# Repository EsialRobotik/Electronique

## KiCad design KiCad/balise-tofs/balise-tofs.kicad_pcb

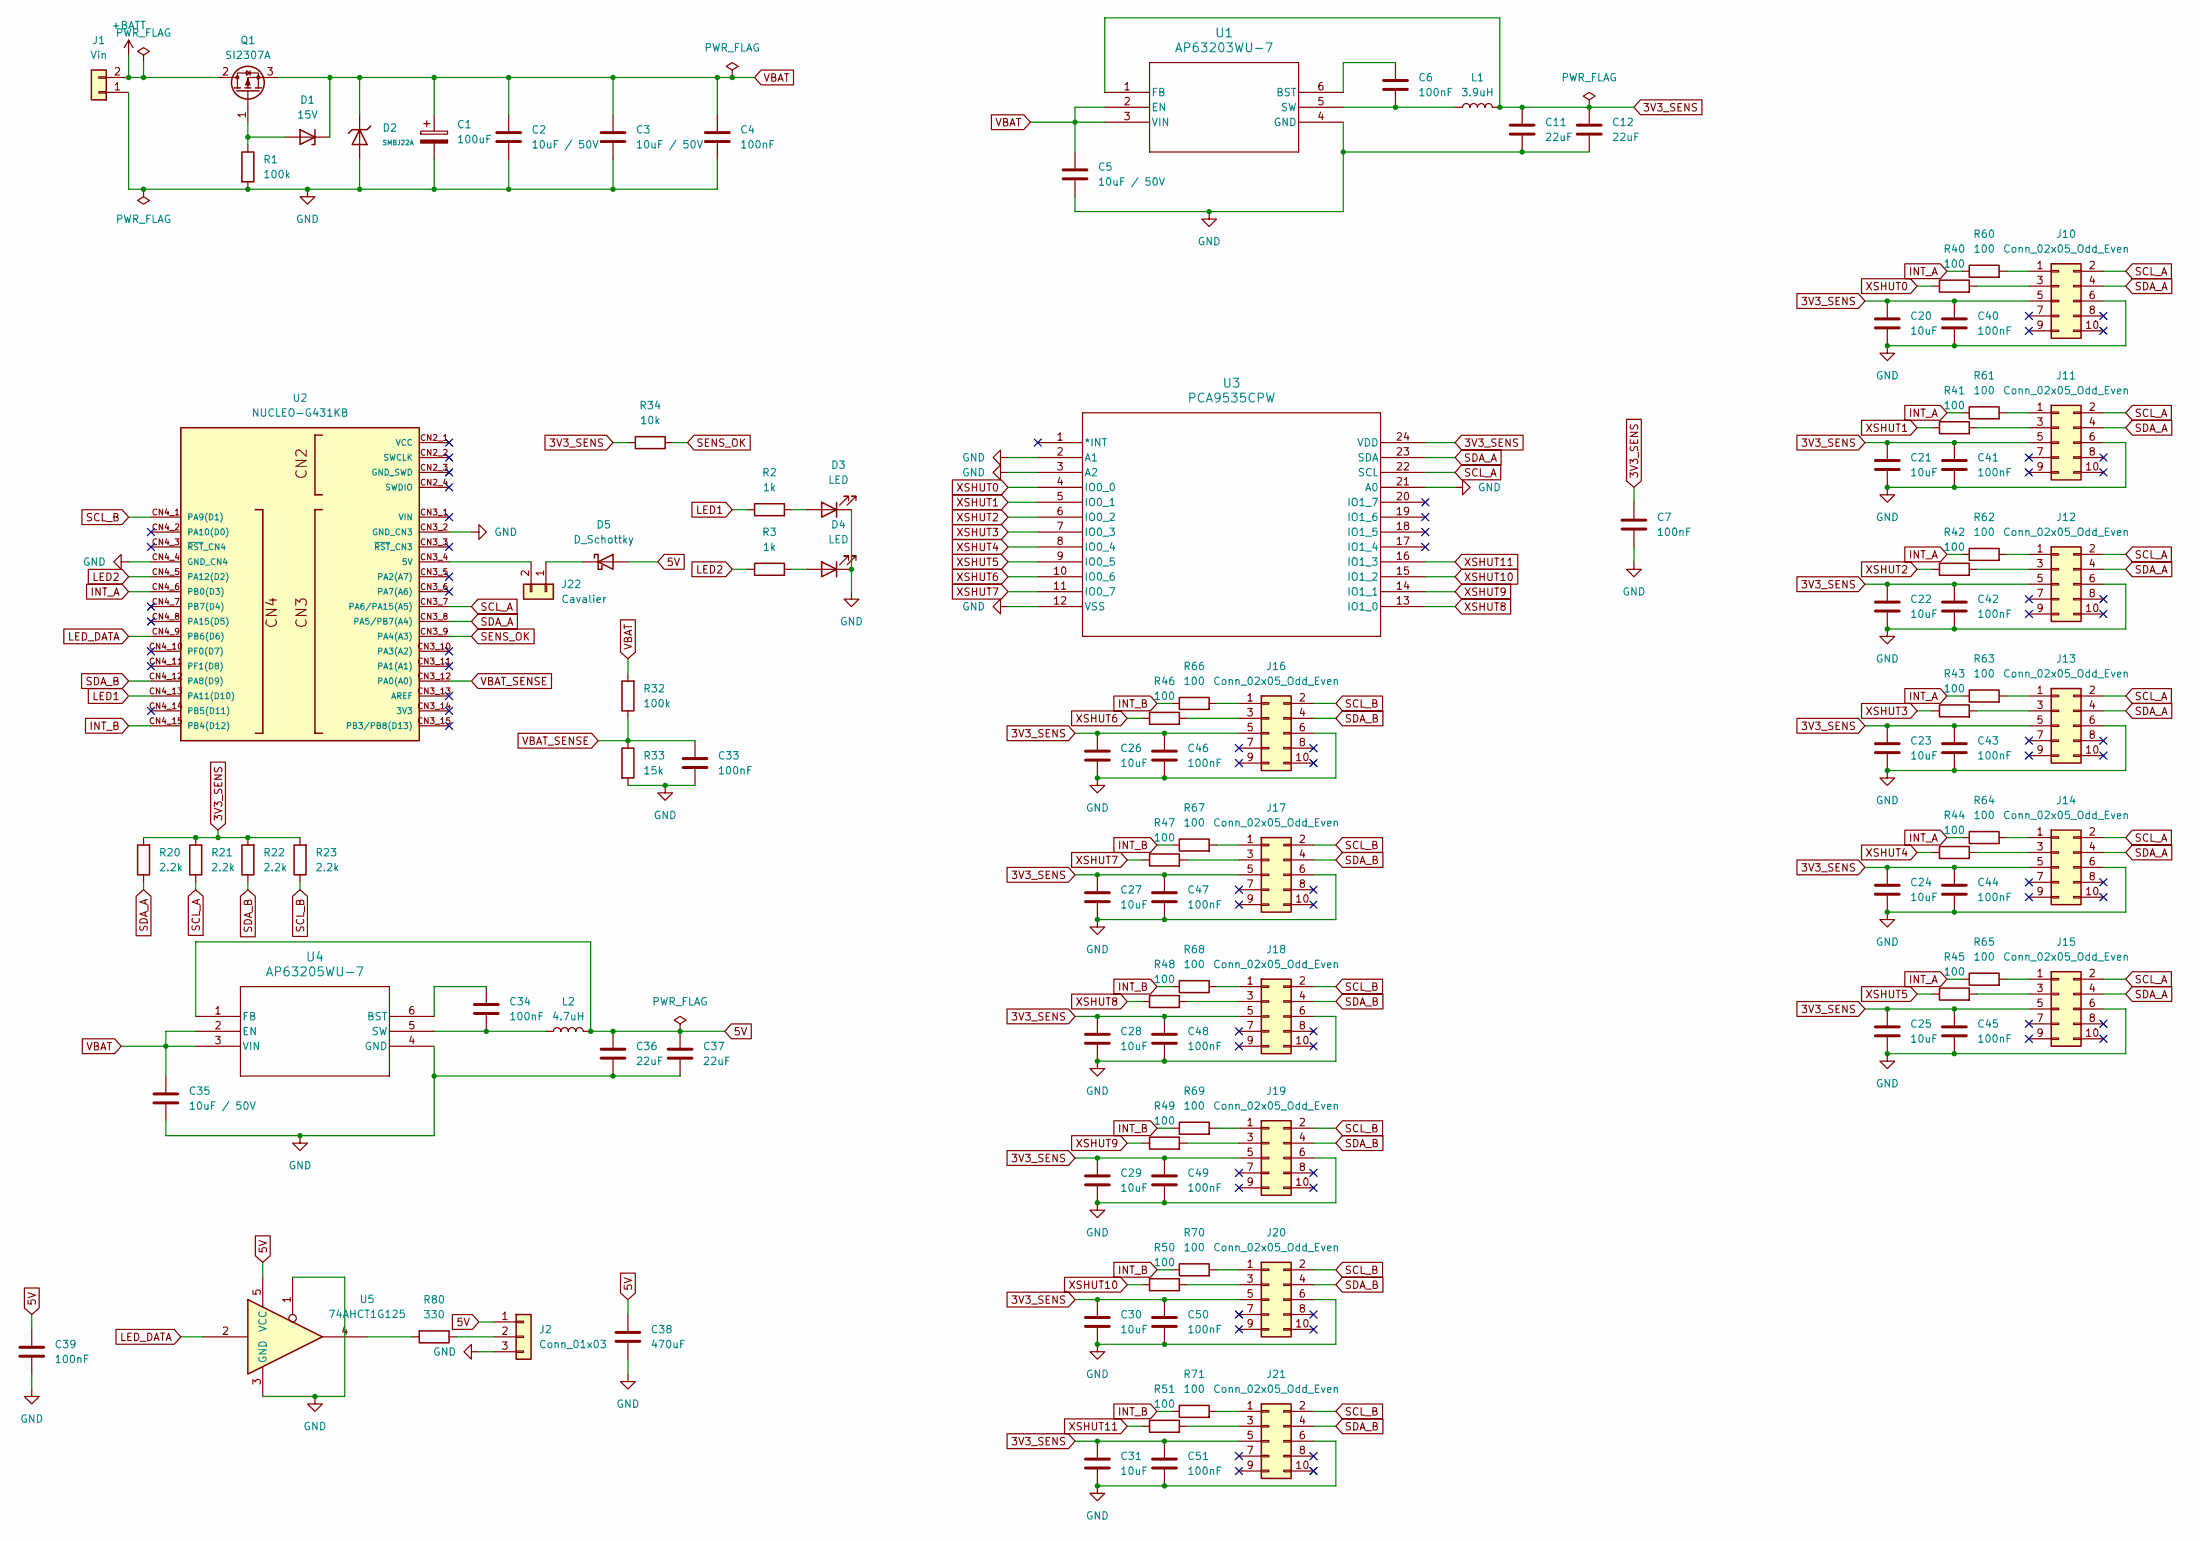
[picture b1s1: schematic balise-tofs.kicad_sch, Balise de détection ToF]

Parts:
C1: 100uF; CP_Elec_8x10.5; LCSC C165580
C2, C3, C5, C35: 10uF / 50V; C_1210_3225Metric; LCSC C138687
C4, C6, C7, C33, C34, C39, C40, C41, C42, C43, C44, C45, C46, C47, C48, C49, C50, C51: 100nF; C_0603_1608Metric; LCSC C14663
C11, C12, C36, C37: 22uF; C_1210_3225Metric; LCSC C52306
C20, C21, C22, C23, C24, C25, C26, C27, C28, C29, C30, C31: 10uF; C_0805_2012Metric; LCSC C15850
C38: 470uF; CP_Elec_8x10.5; LCSC C165531
D1: 15V; D_SOD-123; LCSC C173427
D2: SMBJ22A; D_SMB; Part SMBJ24A; LCSC C151920
D3: LED; LED_0603_1608Metric; LCSC C2986059
D4: LED; LED_0603_1608Metric; LCSC C2286
D5: D_Schottky; D_SOD-123
J1: Vin; JST_XH_B2B-XH-A_1x02_P2.50mm_Vertical; LCSC C158012
J2: Conn_01x03; JST_XH_B3B-XH-A_1x03_P2.50mm_Vertical; LCSC C144394
J10, J11, J12, J13, J14, J15, J16, J17, J18, J19, J20, J21: Conn_02x05_Odd_Even; PinHeader_2x05_P2.54mm_Vertical
J22: Cavalier; JST_XH_B2B-XH-A_1x02_P2.50mm_Vertical; LCSC C158012
L1: 3.9uH; L_Sunlord_SWPA4030S; LCSC C15269
L2: 4.7uH; L_Sunlord_SWPA4030S; LCSC C57269
Q1: SI2307A; SOT-23; LCSC C347490
R1, R32: 100k; R_0603_1608Metric; LCSC C25803
R2, R3: 1k; R_0603_1608Metric; LCSC C21190
R20, R21, R22, R23: 2.2k; R_0603_1608Metric; LCSC C4190
R33: 15k; R_0603_1608Metric; LCSC C22809
R34: 10k; R_0603_1608Metric; LCSC C25804
R40, R41, R42, R43, R44, R45, R46, R47, R48, R49, R50, R51, R60, R61, R62, R63, R64, R65, R66, R67, R68, R69, R70, R71: 100; R_0603_1608Metric; LCSC C22775
R80: 330; R_0603_1608Metric; LCSC C23138
U1: AP63203WU-7; AP63203WU-7_DIO; LCSC C780769
U2: NUCLEO-G431KB; MODULE_NUCLEO-G431KB; PARTREV 2; DigiKey_Part_Number 497-19489-ND
U3: PCA9535CPW; SOT355-1_NXP; LCSC C2652292
U4: AP63205WU-7; SOIC_05WU-7_DIO; LCSC C2071056
U5: 74AHCT1G125; SOT-23-5; LCSC C7484

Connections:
3V3_SENS: C7.1, C11.1, C12.1, C20.1, C21.1, C22.1, C23.1, C24.1, C25.1, C26.1, C27.1, C28.1, C29.1, C30.1, C31.1, C40.1, C41.1, C42.1, C43.1, C44.1, C45.1, C46.1, C47.1, C48.1, C49.1, C50.1, C51.1, J10.5, J11.5, J12.5, J13.5, J14.5, J15.5, J16.5, J17.5, J18.5, J19.5, J20.5, J21.5, L1.2, R20.2, R21.2, R22.2, R23.2, R34.1, U1.1 (FB), U3.24 (VDD)
5V: C36.1, C37.1, C38.1, C39.1, D5.2 (A), J2.1, L2.2, U4.1 (FB), U5.5 (VCC)
+BATT: J1.2, Q1.2 (D)
GND: C1.2, C2.2, C3.2, C4.2, C5.2, C7.2, C11.2, C12.2, C20.2, C21.2, C22.2, C23.2, C24.2, C25.2, C26.2, C27.2, C28.2, C29.2, C30.2, C31.2, C33.2, C35.2, C36.2, C37.2, C38.2, C39.2, C40.2, C41.2, C42.2, C43.2, C44.2, C45.2, C46.2, C47.2, C48.2, C49.2, C50.2, C51.2, D2.2, D3.1 (K), D4.1 (K), J1.1, J2.3, J10.6, J11.6, J12.6, J13.6, J14.6, J15.6, J16.6, J17.6, J18.6, J19.6, J20.6, J21.6, R1.2, R33.2, U1.4 (GND), U2.CN3_2 (GND_CN3), U2.CN4_4 (GND_CN4), U3.2 (A1), U3.3 (A2), U3.12 (VSS), U3.21 (A0), U4.4 (GND), U5.1, U5.3 (GND)
INT_A: R60.1, R61.1, R62.1, R63.1, R64.1, R65.1, U2.CN4_6 (PB0(D3))
INT_B: R66.1, R67.1, R68.1, R69.1, R70.1, R71.1, U2.CN4_15 (PB4(D12))
LED1: R2.1, U2.CN4_13 (PA11(D10))
LED2: R3.1, U2.CN4_5 (PA12(D2))
LED_DATA: U2.CN4_9 (PB6(D6)), U5.2
unnamed: D1.2 (A), Q1.1 (G), R1.1
unnamed: D3.2 (A), R2.2
unnamed: D4.2 (A), R3.2
unnamed: D5.1 (K), J22.1
unnamed: J2.2, R80.1
unnamed: J10.1, R60.2
unnamed: J10.3, R40.2
unnamed: J11.1, R61.2
unnamed: J11.3, R41.2
unnamed: J12.1, R62.2
unnamed: J12.3, R42.2
unnamed: J13.1, R63.2
unnamed: J13.3, R43.2
unnamed: J14.1, R64.2
unnamed: J14.3, R44.2
unnamed: J15.1, R65.2
unnamed: J15.3, R45.2
unnamed: J16.1, R66.2
unnamed: J16.3, R46.2
unnamed: J17.1, R67.2
unnamed: J17.3, R47.2
unnamed: J18.1, R68.2
unnamed: J18.3, R48.2
unnamed: J19.1, R69.2
unnamed: J19.3, R49.2
unnamed: J20.1, R70.2
unnamed: J20.3, R50.2
unnamed: J21.1, R71.2
unnamed: J21.3, R51.2
unnamed: J22.2, U2.CN3_4 (5V)
unnamed: R80.2, U5.4
unnamed: C6.1, U1.6 (BST)
unnamed: C6.2, L1.1, U1.5 (SW)
unnamed: C34.1, U4.6 (BST)
unnamed: C34.2, L2.1, U4.5 (SW)
SCL_A: J10.2, J11.2, J12.2, J13.2, J14.2, J15.2, R21.1, U2.CN3_7 (PA6/PA15(A5)), U3.22 (SCL)
SCL_B: J16.2, J17.2, J18.2, J19.2, J20.2, J21.2, R23.1, U2.CN4_1 (PA9(D1))
SDA_A: J10.4, J11.4, J12.4, J13.4, J14.4, J15.4, R20.1, U2.CN3_8 (PA5/PB7(A4)), U3.23 (SDA)
SDA_B: J16.4, J17.4, J18.4, J19.4, J20.4, J21.4, R22.1, U2.CN4_12 (PA8(D9))
SENS_OK: R34.2, U2.CN3_9 (PA4(A3))
VBAT: C1.1, C2.1, C3.1, C4.1, C5.1, C35.1, D1.1 (K), D2.1, Q1.3 (S), R32.2, U1.2 (EN), U1.3 (VIN), U4.2 (EN), U4.3 (VIN)
VBAT_SENSE: C33.1, R32.1, R33.1, U2.CN3_12 (PA0(A0))
XSHUT0: R40.1, U3.4 (IO0_0)
XSHUT1: R41.1, U3.5 (IO0_1)
XSHUT2: R42.1, U3.6 (IO0_2)
XSHUT3: R43.1, U3.7 (IO0_3)
XSHUT4: R44.1, U3.8 (IO0_4)
XSHUT5: R45.1, U3.9 (IO0_5)
XSHUT6: R46.1, U3.10 (IO0_6)
XSHUT7: R47.1, U3.11 (IO0_7)
XSHUT8: R48.1, U3.13 (IO1_0)
XSHUT9: R49.1, U3.14 (IO1_1)
XSHUT10: R50.1, U3.15 (IO1_2)
XSHUT11: R51.1, U3.16 (IO1_3)

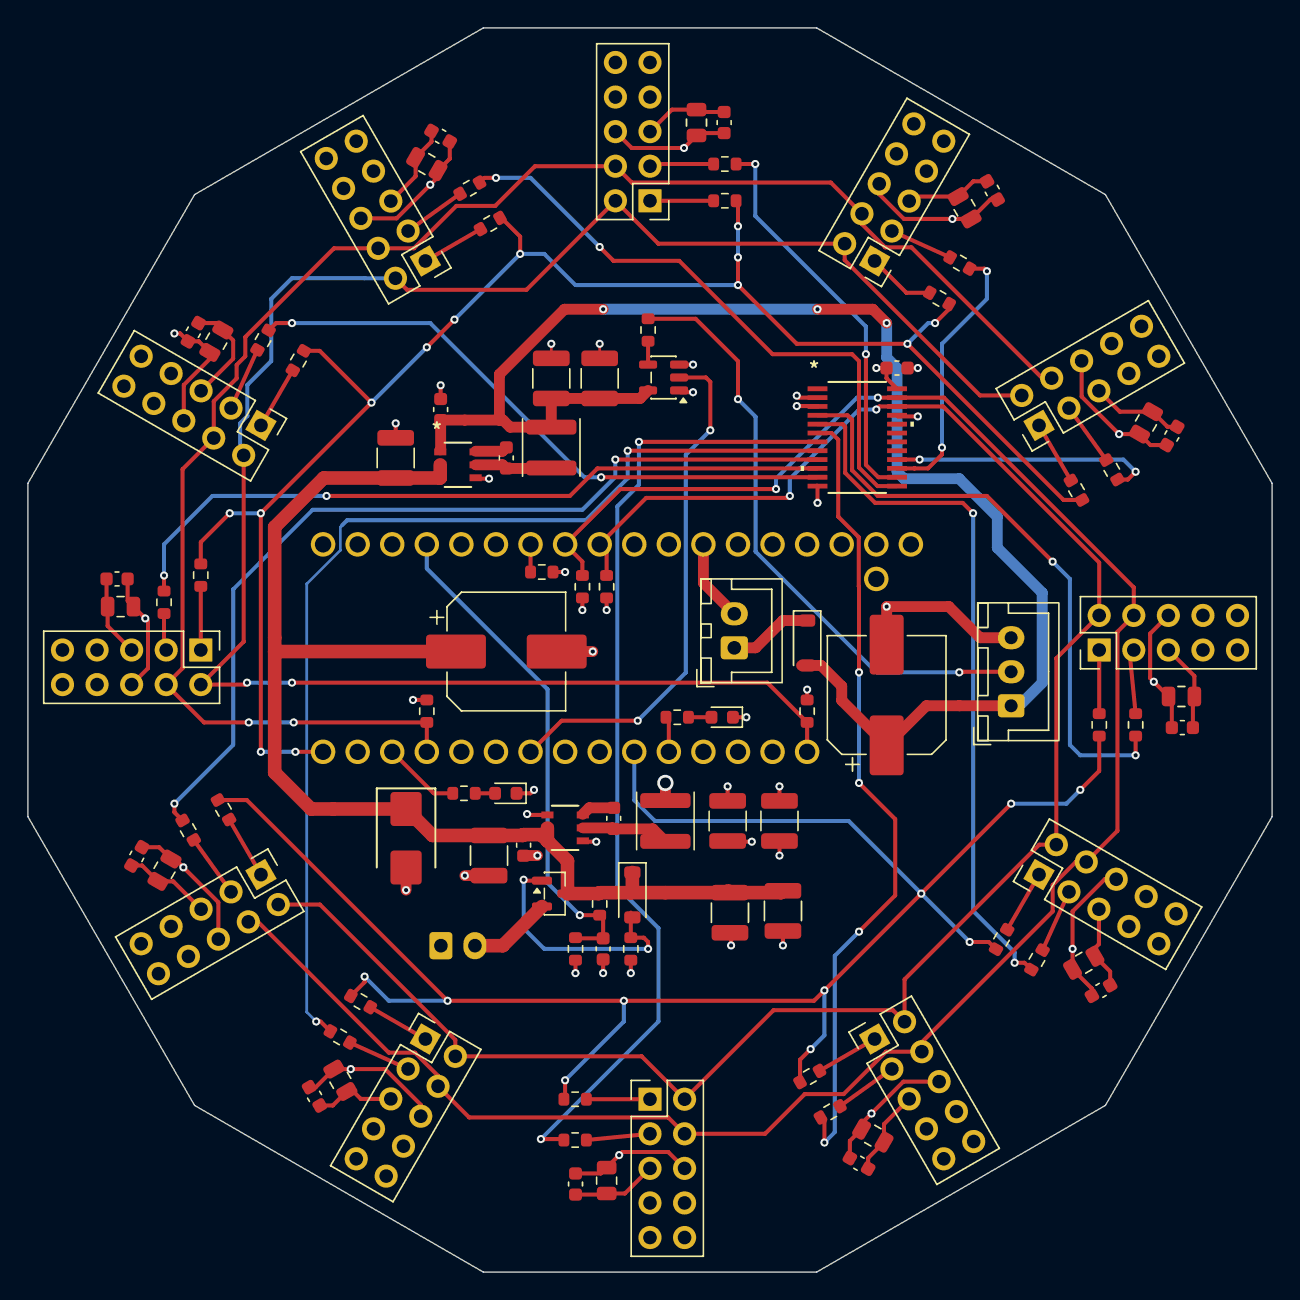
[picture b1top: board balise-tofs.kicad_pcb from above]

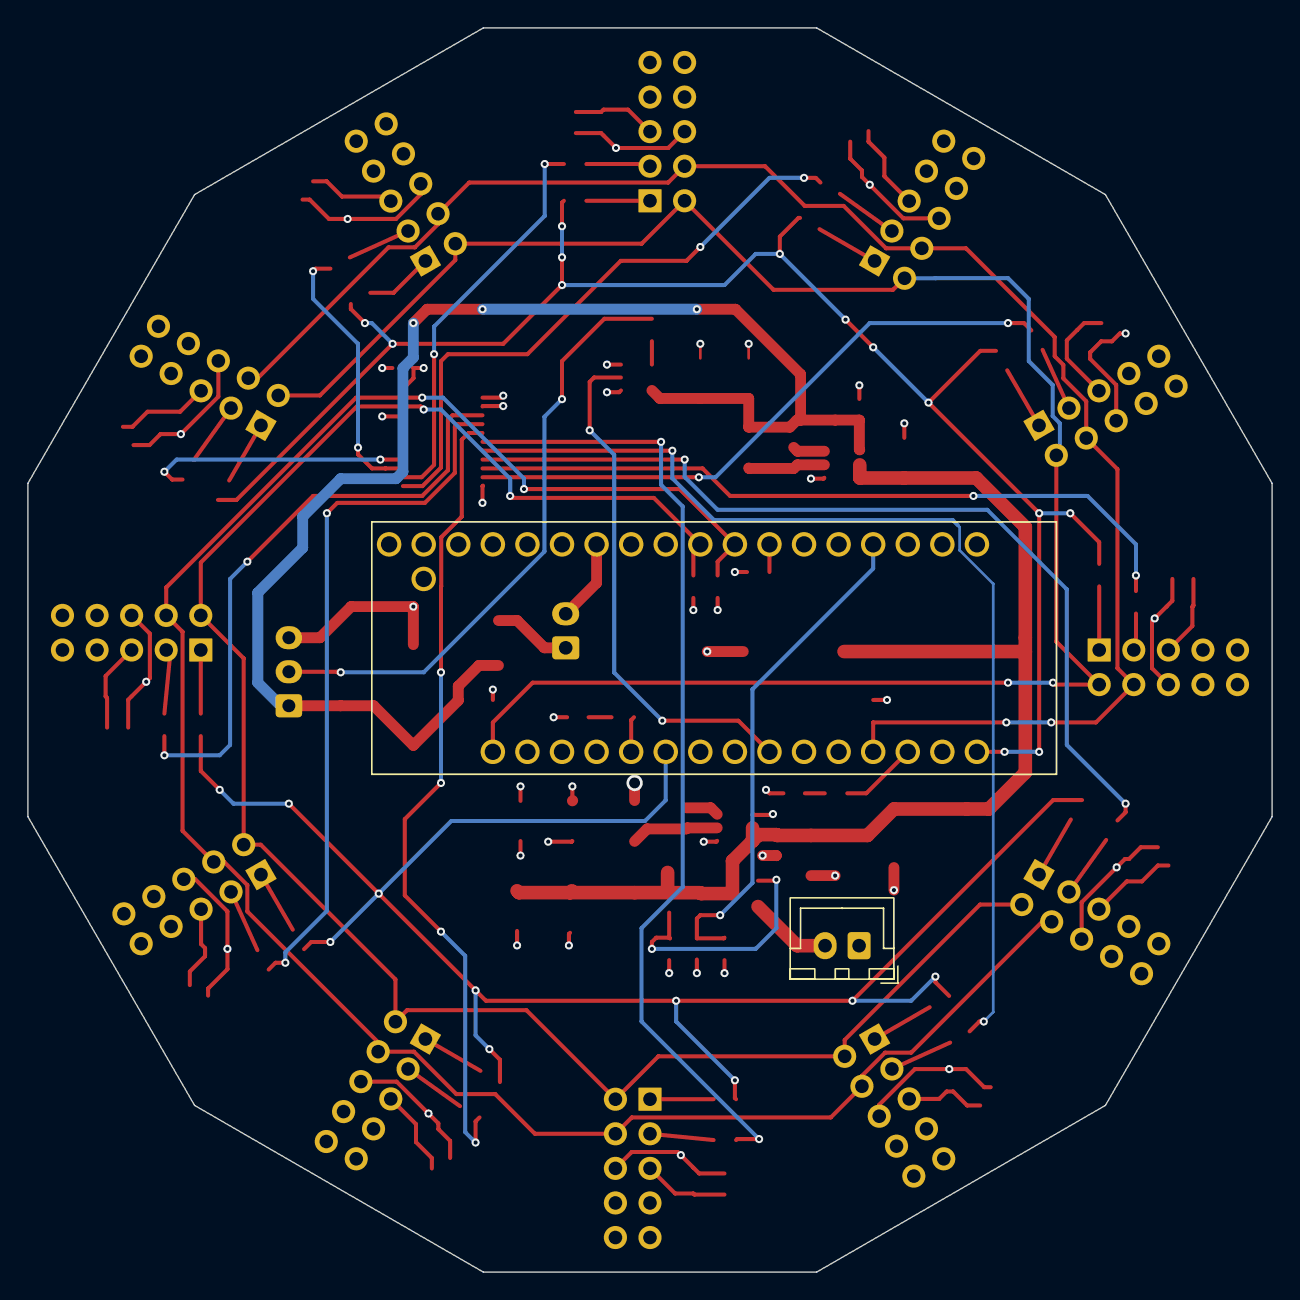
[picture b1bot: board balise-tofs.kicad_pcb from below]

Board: 4 copper layers, 91.4 x 91.4 mm, 103 parts (2 on the bottom side), 63 nets.

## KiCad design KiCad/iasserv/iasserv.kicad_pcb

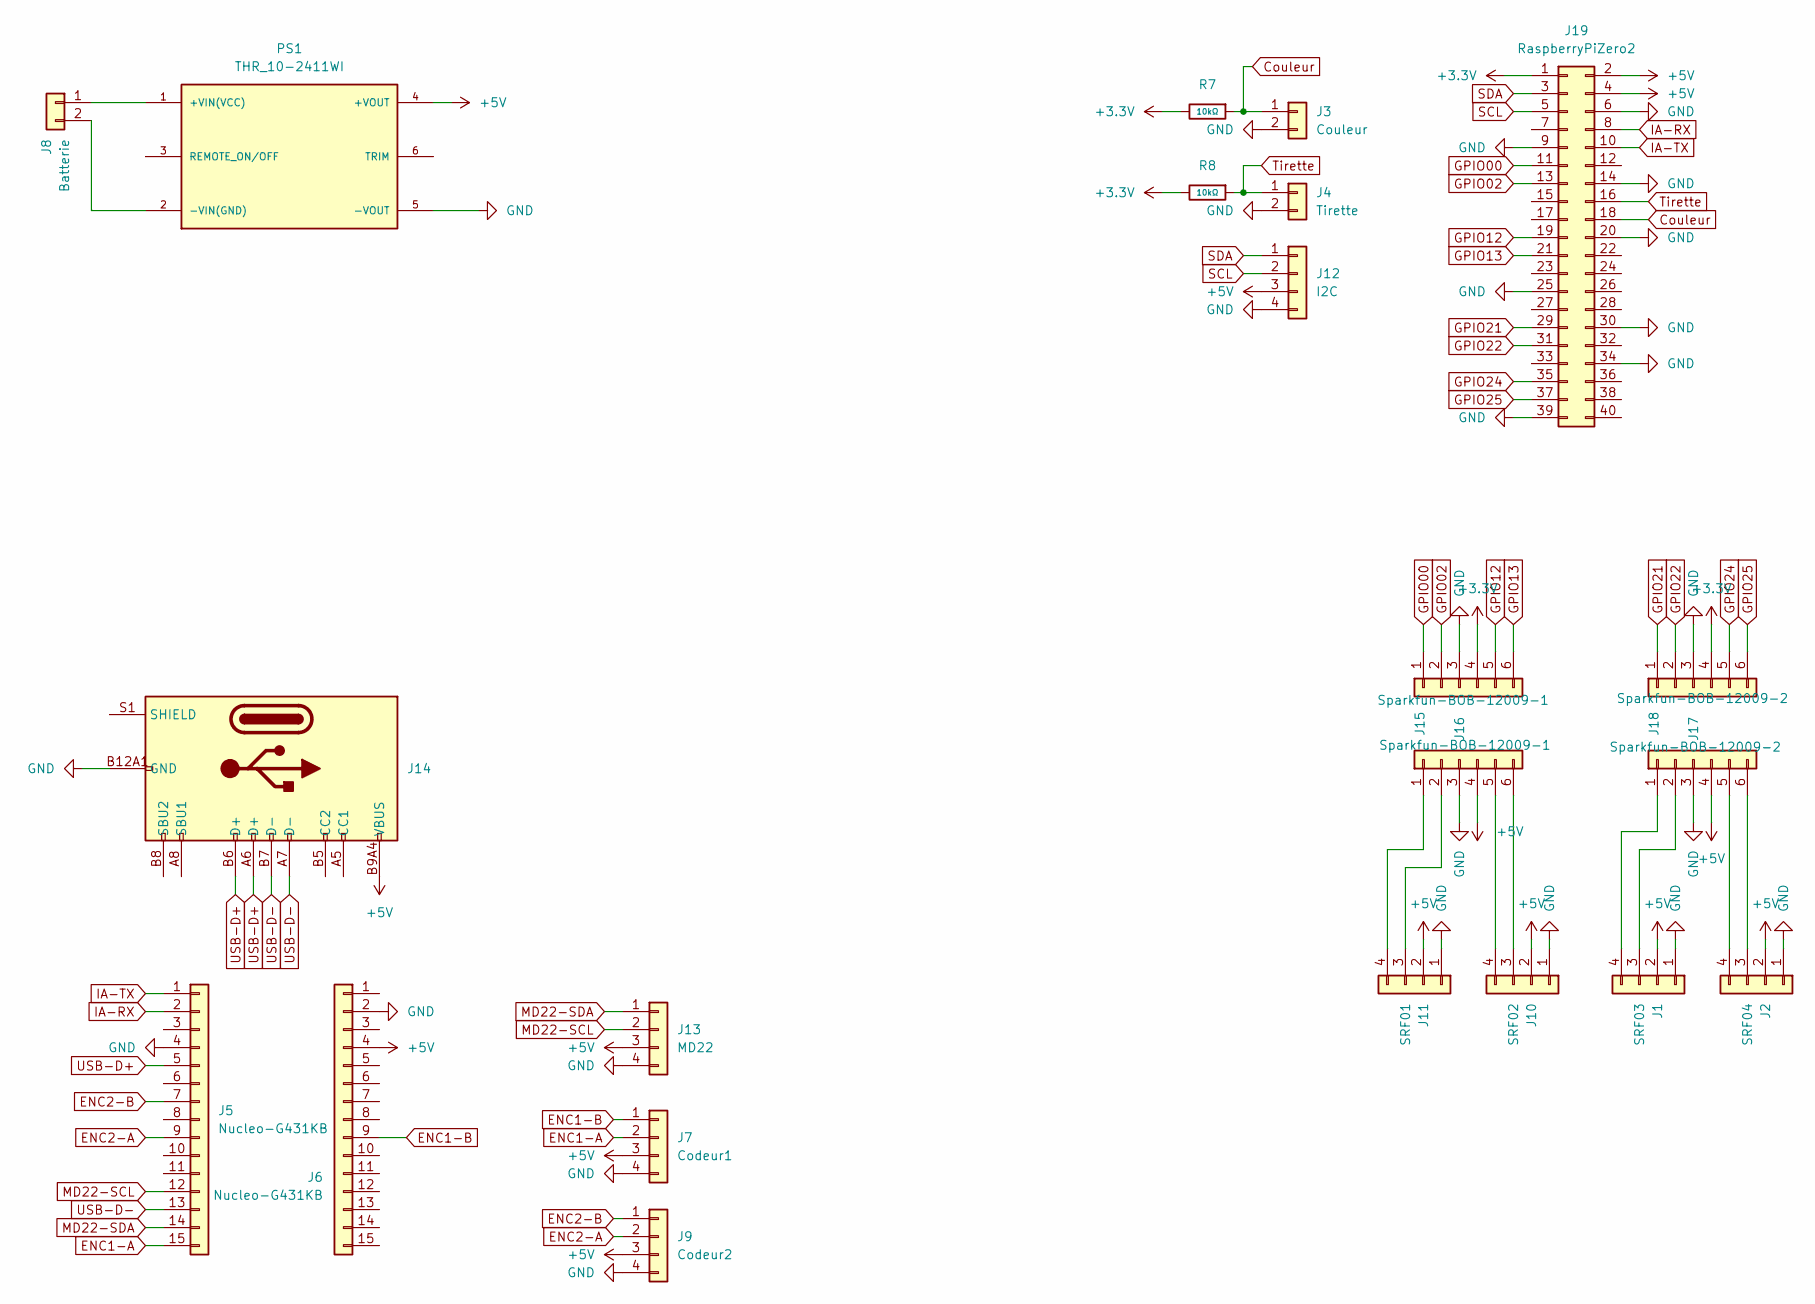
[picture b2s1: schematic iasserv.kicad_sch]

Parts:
J1: SRF03; JST_XH_B4B-XH-A_1x04_P2.50mm_Vertical
J2: SRF04; JST_XH_B4B-XH-A_1x04_P2.50mm_Vertical
J3: Couleur; JST_XH_B2B-XH-A_1x02_P2.50mm_Vertical
J4: Tirette; JST_XH_B2B-XH-A_1x02_P2.50mm_Vertical
J5, J6: Nucleo-G431KB; PinHeader_1x15_P2.54mm_Vertical
J7: Codeur1; JST_XH_B4B-XH-A_1x04_P2.50mm_Vertical
J8: Batterie; JST_XH_B2B-XH-A_1x02_P2.50mm_Vertical
J9: Codeur2; JST_XH_B4B-XH-A_1x04_P2.50mm_Vertical
J10: SRF02; JST_XH_B4B-XH-A_1x04_P2.50mm_Vertical
J11: SRF01; JST_XH_B4B-XH-A_1x04_P2.50mm_Vertical
J12: I2C; JST_XH_B4B-XH-A_1x04_P2.50mm_Vertical
J13: MD22; JST_XH_B4B-XH-A_1x04_P2.50mm_Vertical
J14: Connector, USB-TYPE-C-16P; TYPE-C-SMD_HX-TYPE-C-16PIN; LCSC C2927039
J15, J16: Sparkfun-BOB-12009-1; PinHeader_1x06_P2.54mm_Vertical
J17, J18: Sparkfun-BOB-12009-2; PinHeader_1x06_P2.54mm_Vertical
J19: RaspberryPiZero2; PinHeader_2x20_P2.54mm_Vertical
PS1: THR_10-2411WI; CONV_THR_10-2411WI; PARTREV September 21, 2021
R7, R8: 10kΩ; R_0603; Overload Voltage (Max) 75V; Tolerance ±1%; Part 0603WAF1002T5E; LCSC C25804

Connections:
+3.3V: J15.4, J18.4, J19.1, R7.2, R8.2
+5V: J1.2, J2.2, J6.4, J7.3, J9.3, J10.2, J11.2, J12.3, J13.3, J14.A9B4 (VBUS), J14.B9A4 (VBUS), J16.4, J17.4, J19.2, J19.4, PS1.4 (+VOUT)
Couleur: J3.1, J19.18, R7.1
ENC1-A: J5.15, J7.2
ENC1-B: J6.9, J7.1
ENC2-A: J5.9, J9.2
ENC2-B: J5.7, J9.1
GND: J1.1, J2.1, J3.2, J4.2, J5.4, J6.2, J7.4, J9.4, J10.1, J11.1, J12.4, J13.4, J14.A12B1 (GND), J14.B12A1 (GND), J15.3, J16.3, J17.3, J18.3, J19.6, J19.9, J19.14, J19.20, J19.25, J19.30, J19.34, J19.39, PS1.5 (-VOUT)
GPIO00: J15.1, J19.11
GPIO02: J15.2, J19.13
GPIO12: J15.5, J19.19
GPIO13: J15.6, J19.21
GPIO21: J18.1, J19.29
GPIO22: J18.2, J19.31
GPIO24: J18.5, J19.35
GPIO25: J18.6, J19.37
IA-RX: J5.2, J19.8
IA-TX: J5.1, J19.10
MD22-SCL: J5.12, J13.2
MD22-SDA: J5.14, J13.1
unnamed: J1.3, J17.2
unnamed: J1.4, J17.1
unnamed: J8.1, PS1.1 (+VIN(VCC))
unnamed: J8.2, PS1.2 (-VIN(GND))
unnamed: J10.3, J16.6
unnamed: J10.4, J16.5
unnamed: J11.3, J16.2
unnamed: J11.4, J16.1
unnamed: J2.4, J17.5
unnamed: J2.3, J17.6
SCL: J12.2, J19.5
SDA: J12.1, J19.3
Tirette: J4.1, J19.16, R8.1
USB-D+: J5.5, J14.A6 (D+), J14.B6 (D+)
USB-D-: J5.13, J14.A7 (D-), J14.B7 (D-)

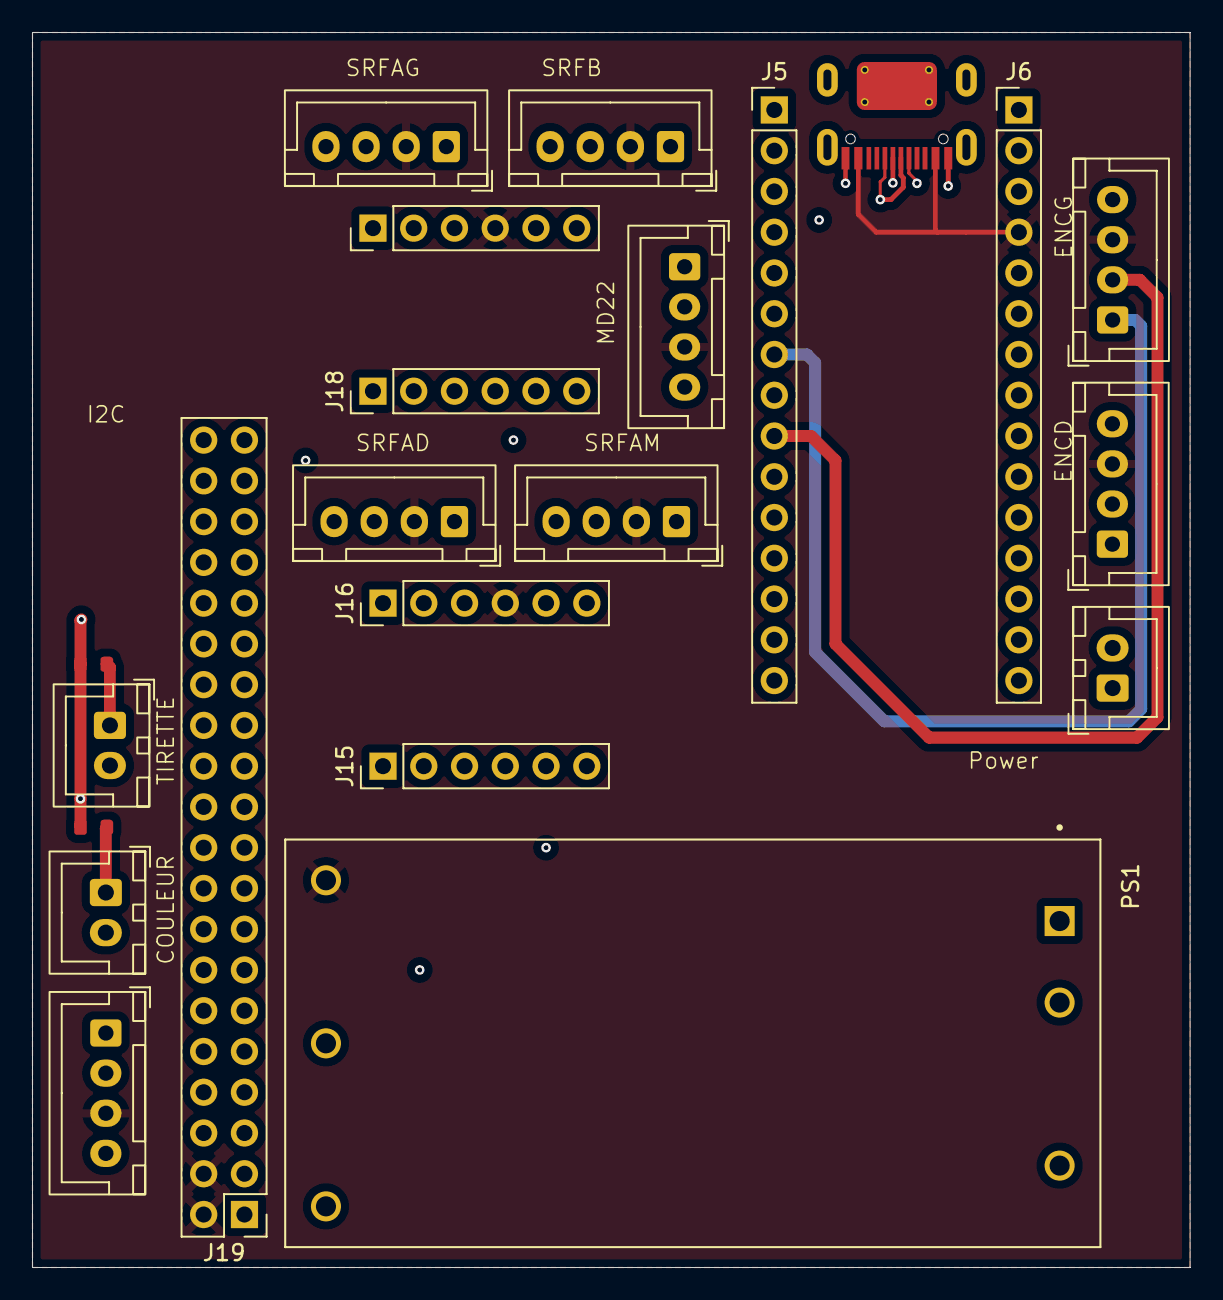
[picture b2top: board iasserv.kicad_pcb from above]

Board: 4 copper layers, 72.1 x 77.0 mm, 22 parts (0 on the bottom side), 35 nets.

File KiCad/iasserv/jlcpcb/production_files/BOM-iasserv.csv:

Comment,Designator,Footprint,LCSC,Quantity
SRF03,"J1,J10,J11,J12,J13,J2,J7,J9",JST_XH_B4B-XH-A_1x04_P2.50mm_Vertical,C144395,8
Couleur,"J3,J4,J8",JST_XH_B2B-XH-A_1x02_P2.50mm_Vertical,C158012,3
"Connector, USB-TYPE-C-16P",J14,TYPE-C-SMD_HX-TYPE-C-16PIN,C165948,1
Sparkfun-BOB-12009-1,"J15,J16,J17,J18",PinHeader_1x06_P2.54mm_Vertical,C18078129,4
Nucleo-G431KB,"J5,J6",PinHeader_1x15_P2.54mm_Vertical,C18078136,2
10kΩ,"R7,R8",R_0603,C25804,2

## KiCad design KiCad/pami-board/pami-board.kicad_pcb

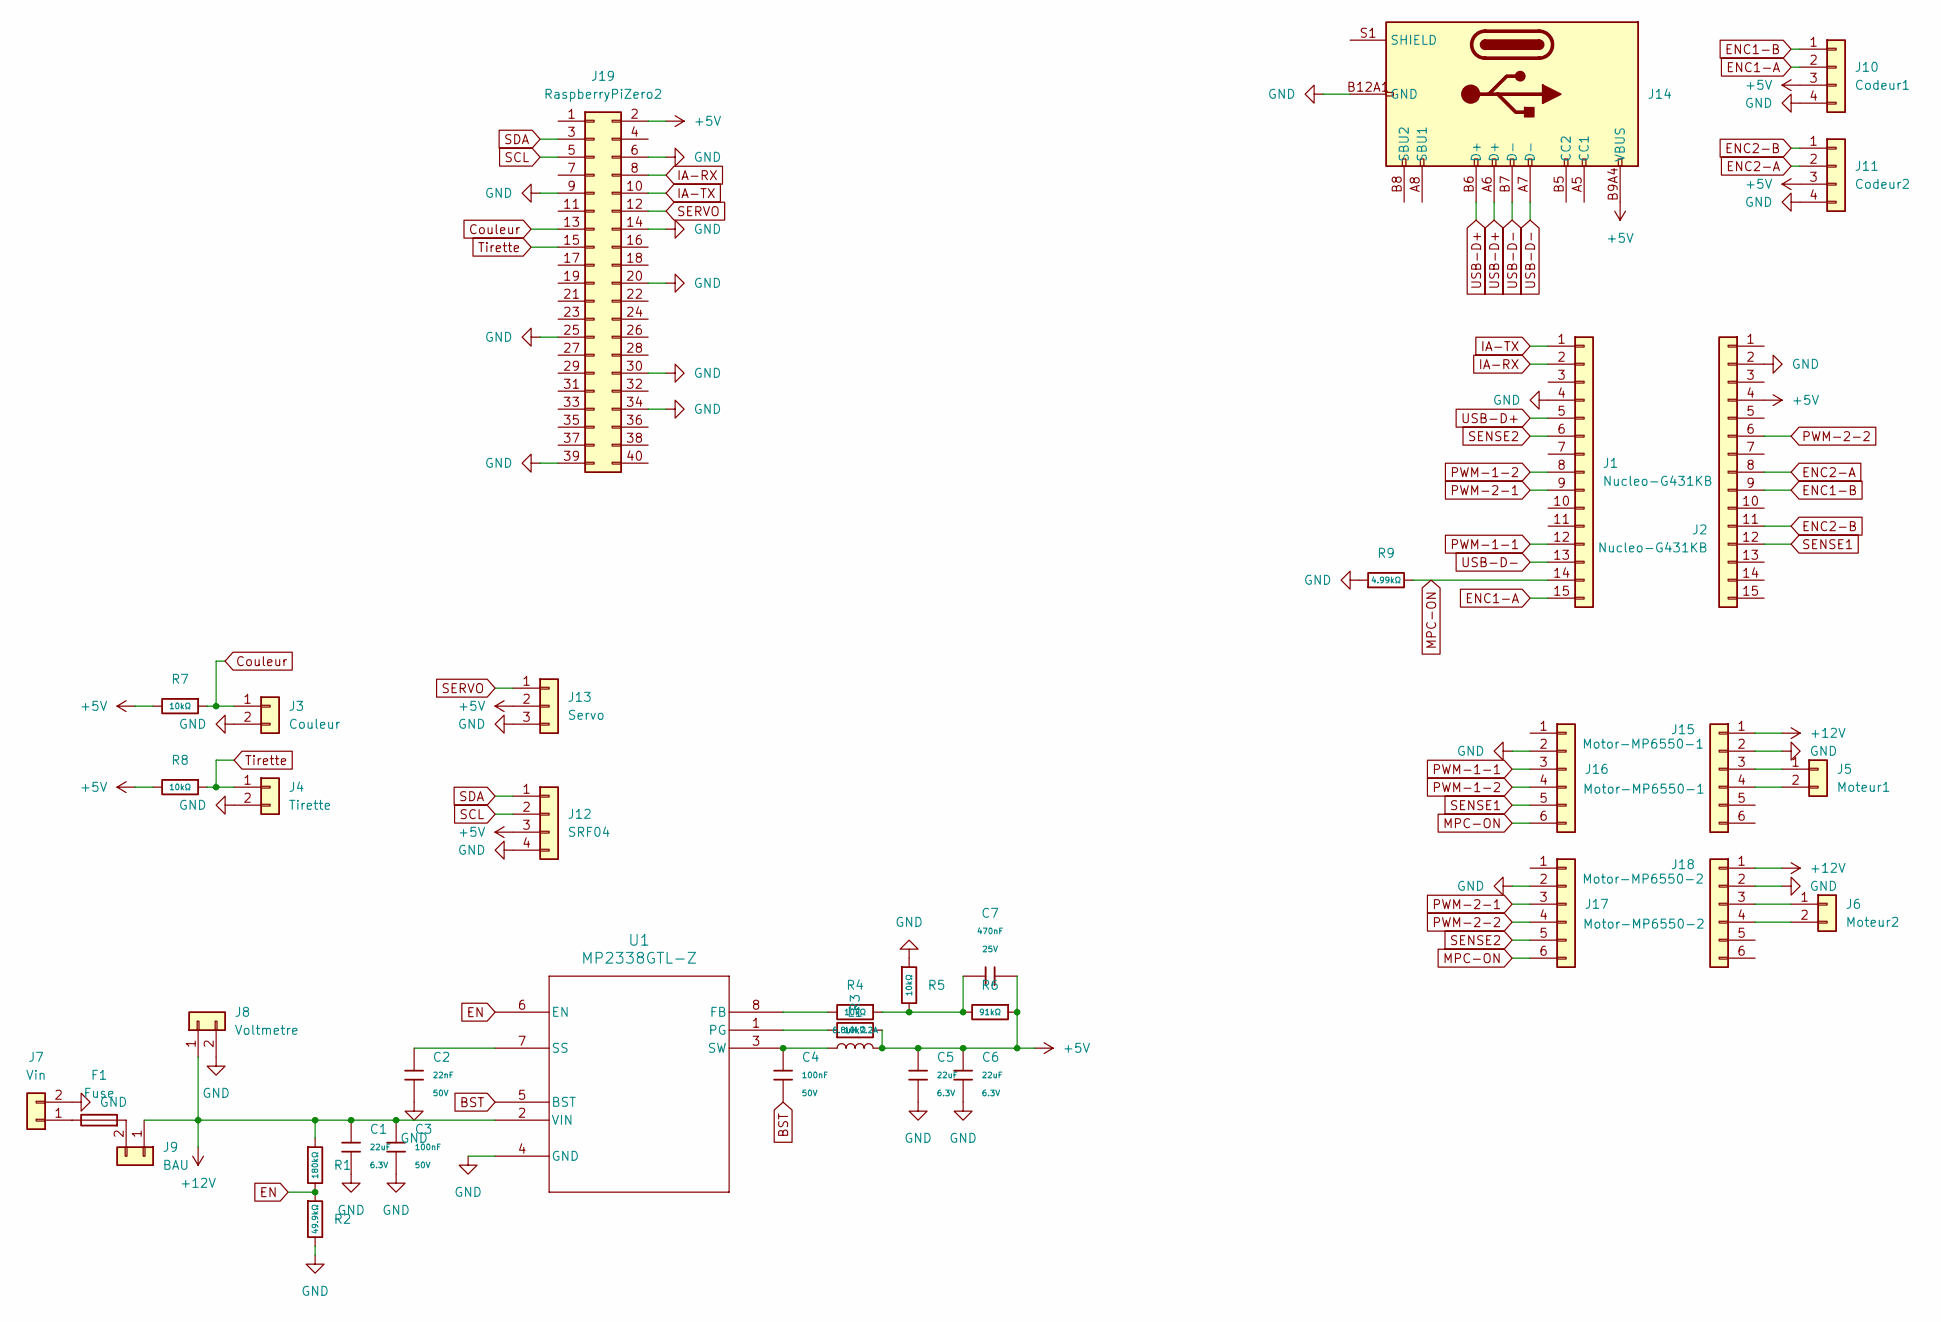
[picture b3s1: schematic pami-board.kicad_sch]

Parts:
C1, C5, C6: 22uF; C_0603; Voltage Rated 6.3V; Tolerance ±20%; Part CL10A226MQ8NRNC; LCSC C59461
C2: 22nF; C_0603; Voltage Rated 50V; Tolerance ±10%; Part CL10B223KB8NNNC; LCSC C21122
C3, C4: 100nF; C_0603; Voltage Rated 50V; Tolerance ±10%; Part CC0603KRX7R9BB104; LCSC C14663
C7: 470nF; C_0603; Voltage Rated 25V; Tolerance ±10%; Part CL10B474KA8NNNC; LCSC C1623
F1: Fuse; Fuse-Holder-5x20
J1, J2: Nucleo-G431KB; PinHeader_1x15_P2.54mm_Vertical
J3: Couleur; JST_XH_B2B-XH-A_1x02_P2.50mm_Vertical
J4: Tirette; JST_XH_B2B-XH-A_1x02_P2.50mm_Vertical
J5: Moteur1; JST_XH_B2B-XH-A_1x02_P2.50mm_Vertical
J6: Moteur2; JST_XH_B2B-XH-A_1x02_P2.50mm_Vertical
J7: Vin; JST_XH_B2B-XH-A_1x02_P2.50mm_Vertical
J8: Voltmetre; JST_XH_B2B-XH-A_1x02_P2.50mm_Vertical
J9: BAU; JST_XH_B2B-XH-A_1x02_P2.50mm_Vertical
J10: Codeur1; JST_XH_B4B-XH-A_1x04_P2.50mm_Vertical
J11: Codeur2; JST_XH_B4B-XH-A_1x04_P2.50mm_Vertical
J12: SRF04; JST_XH_B4B-XH-A_1x04_P2.50mm_Vertical
J13: Servo; JST_XH_B3B-XH-A_1x03_P2.50mm_Vertical
J14: Connector, USB-TYPE-C-16P; TYPE-C-SMD_HX-TYPE-C-16PIN; LCSC C2927039
J15, J16: Motor-MP6550-1; PinHeader_1x06_P2.54mm_Vertical
J17, J18: Motor-MP6550-2; PinHeader_1x06_P2.54mm_Vertical
J19: RaspberryPiZero2; PinHeader_2x20_P2.54mm_Vertical
L1: 6.8uH,7.2A; L_12x12mm_H4.5mm; Tolerance ±10%; Part CMI321609U4R7KT; LCSC C1049
R1: 180kΩ; R_0603; Overload Voltage (Max) 75V; Tolerance ±1%; Part 0603WAF1803T5E; LCSC C22827
R2: 49.9kΩ; R_0603; Overload Voltage (Max) 75V; Tolerance ±1%; Part 0603WAF4992T5E; LCSC C23184
R3, R4, R5, R7, R8: 10kΩ; R_0603; Overload Voltage (Max) 75V; Tolerance ±1%; Part 0603WAF1002T5E; LCSC C25804
R6: 91kΩ; R_0603; Overload Voltage (Max) 75V; Tolerance ±1%; Part 0603WAF9102T5E; LCSC C23265
R9: 4.99kΩ; R_0603; Overload Voltage (Max) 75V; Tolerance ±1%; Part 0603WAF4991T5E; LCSC C23046
U1: MP2338GTL-Z; SOT-583-8

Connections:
+5V: C5.1, C6.1, C7.2, J2.4, J10.3, J11.3, J12.3, J13.2, J14.A9B4 (VBUS), J14.B9A4 (VBUS), J19.2, L1.2, R3.2, R6.1, R7.2, R8.2
+12V: C1.1, C3.1, J8.1, J9.1, J15.1, J18.1, R1.1, U1.2 (VIN)
BST: C4.2, U1.5 (BST)
Couleur: J3.1, J19.13, R7.1
EN: R1.2, R2.1, U1.6 (EN)
ENC1-A: J1.15, J10.2
ENC1-B: J2.9, J10.1
ENC2-A: J2.8, J11.2
ENC2-B: J2.11, J11.1
GND: C1.2, C2.2, C3.2, C5.2, C6.2, J1.4, J2.2, J3.2, J4.2, J7.2, J8.2, J10.4, J11.4, J12.4, J13.3, J14.A12B1 (GND), J14.B12A1 (GND), J15.2, J16.2, J17.2, J18.2, J19.6, J19.9, J19.14, J19.20, J19.25, J19.30, J19.34, J19.39, R2.2, R5.1, R9.1, U1.4 (GND)
IA-RX: J1.2, J19.8
IA-TX: J1.1, J19.10
MPC-ON: J1.14, J16.6, J17.6, R9.2
unnamed: C7.1, R4.1, R5.2, R6.2
unnamed: F1.1, J7.1
unnamed: F1.2, J9.2
unnamed: J5.1, J15.3
unnamed: J5.2, J15.4
unnamed: J6.1, J18.3
unnamed: J6.2, J18.4
unnamed: R4.2, U1.8 (FB)
unnamed: R3.1, U1.1 (PG)
unnamed: C2.1, U1.7 (SS)
unnamed: C4.1, L1.1, U1.3 (SW)
PWM-1-1: J1.12, J16.3
PWM-1-2: J1.8, J16.4
PWM-2-1: J1.9, J17.3
PWM-2-2: J2.6, J17.4
SCL: J12.2, J19.5
SDA: J12.1, J19.3
SENSE1: J2.12, J16.5
SENSE2: J1.6, J17.5
SERVO: J13.1, J19.12
Tirette: J4.1, J19.15, R8.1
USB-D+: J1.5, J14.A6 (D+), J14.B6 (D+)
USB-D-: J1.13, J14.A7 (D-), J14.B7 (D-)

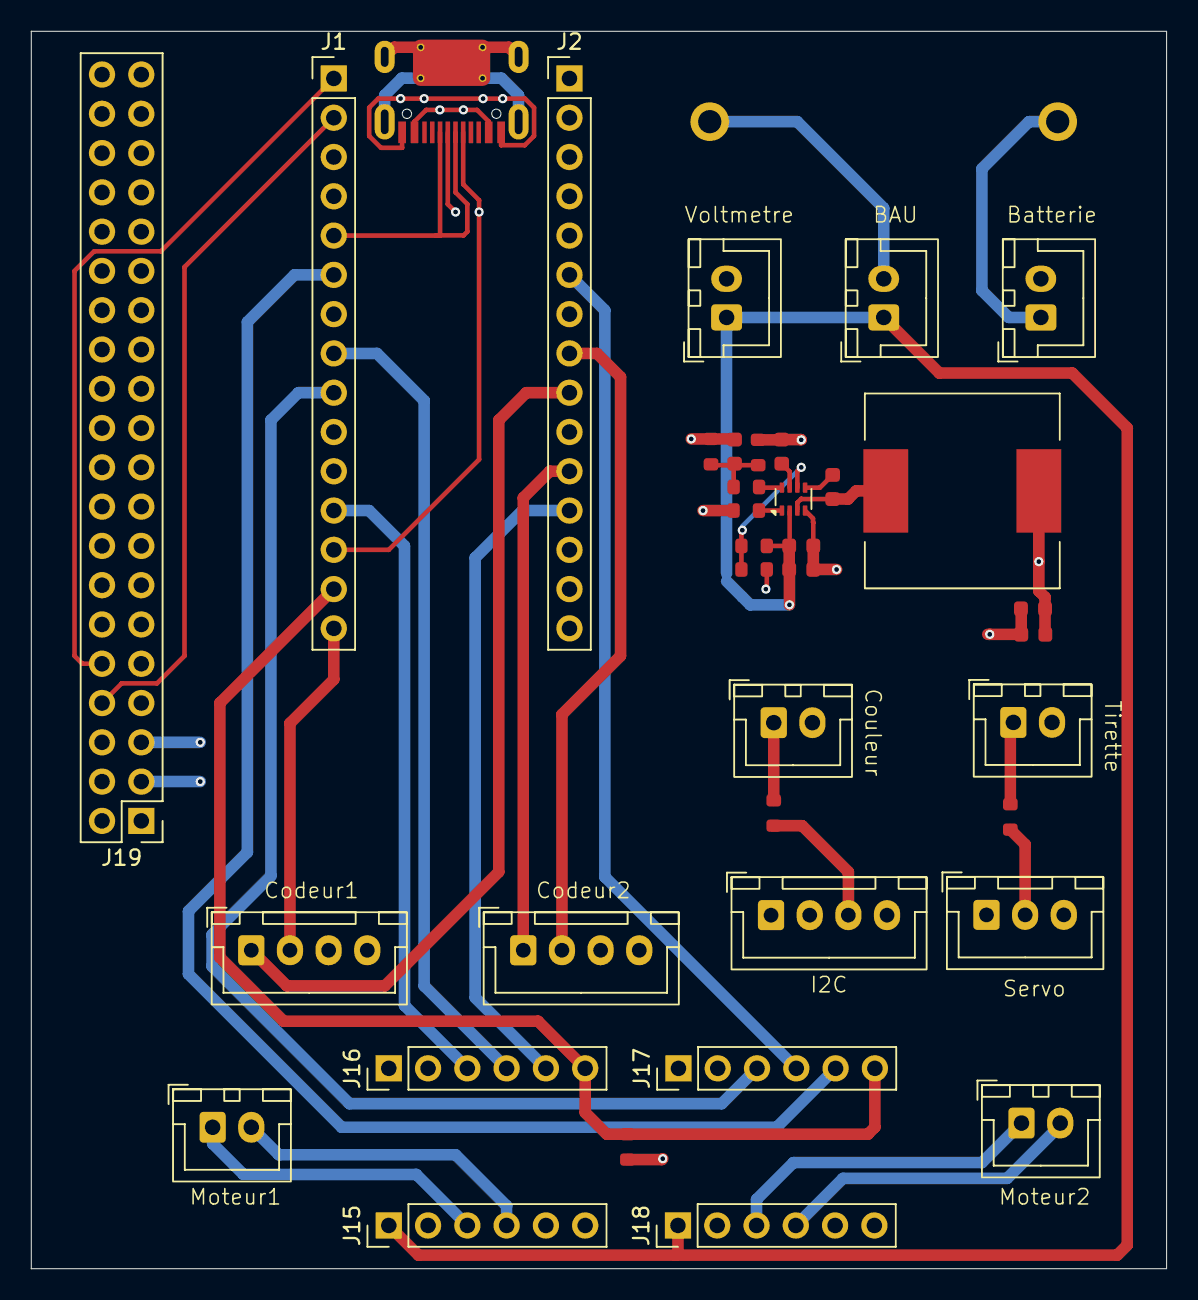
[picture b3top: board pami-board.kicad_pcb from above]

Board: 4 copper layers, 73.4 x 80.0 mm, 38 parts (0 on the bottom side), 36 nets.

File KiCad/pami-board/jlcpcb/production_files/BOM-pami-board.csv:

Comment,Designator,Footprint,LCSC,Quantity
Servo,J13,JST_XH_B3B-XH-A_1x03_P2.50mm_Vertical,C144394,1
Codeur1,"J10,J11,J12",JST_XH_B4B-XH-A_1x04_P2.50mm_Vertical,C144395,3
100nF,"C3,C4",C_0603,C14663,2
Couleur,"J3,J4,J5,J6,J7,J8,J9",JST_XH_B2B-XH-A_1x02_P2.50mm_Vertical,C158012,7
470nF,C7,C_0603,C1623,1
"Connector, USB-TYPE-C-16P",J14,TYPE-C-SMD_HX-TYPE-C-16PIN,C165948,1
Motor-MP6550-1,"J15,J16,J17,J18",PinHeader_1x06_P2.54mm_Vertical,C18078129,4
Nucleo-G431KB,"J1,J2",PinHeader_1x15_P2.54mm_Vertical,C18078136,2
RaspberryPiZero2,J19,PinHeader_2x20_P2.54mm_Vertical,C18078157,1
22nF,C2,C_0603,C21122,1
180kΩ,R1,R_0603,C22827,1
4.99kΩ,R9,R_0603,C23046,1
49.9kΩ,R2,R_0603,C23184,1
91kΩ,R6,R_0603,C23265,1
10kΩ,"R3,R4,R5,R7,R8",R_0603,C25804,5
Fuse,F1,Fuse-Holder-5x20,C3131,1
22uF,"C1,C5,C6",C_0603,C59461,3
MP2338GTL-Z,U1,SOT-583-8,C7210174,1
"6.8uH,7.2A",L1,L_12x12mm_H4.5mm,C7431079,1

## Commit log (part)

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2017-11-12 carte d'alimentation
2017-11-13 utilisation de bornier pour les ARU + plus grosses pistes dans le routage + gerber files
2018-03-04 carte d'asserv
2018-03-12 carte IA
2018-03-27 ajout d'un i2c sur l'asserv et design de l'ia
2018-04-03 IA: Correction des pullup sur les GPIOs
2018-04-04 routage IA + gerber
2019-03-07 carte puissance v2
2019-03-17 puissance IA + carte AX12
2019-03-25 lidar + reset mbed + trou ax12
2019-03-25 gerber files
2019-04-01 fix board et gerber file
2020-02-16 asserv Nucleo
2020-02-23 maj asserv nucelo
2022-10-09 gerber file for IA V2 + new libraries from mouser + Lidar / Ia / Asserv shield project creation
2023-04-02 Cleaning and new cards
2023-11-18 wip: Lidar schematic
2024-01-13 board schematic
2024-01-14 re-route everything
2024-01-14 (re-)use the VCC pin to avoid 90° routes
2024-01-14 add LIDAR board (power&logic)
    from fusetim-lidar-board:
    * wip: Lidar schematic
    * board schematic
    * re-route everything
    * (re-)use the VCC pin to avoid 90° routes
2024-01-14 add(lidar): POWER LED + reduce the board size
2024-12-19 Asserv PAMI board
2025-02-05 ajout BAU et Voltmetre + label
2025-03-15 for impression
2025-03-15 fix court circuit
2025-03-15 update pdf
2025-03-30 fix i2c
2025-03-30 fix name
2025-05-08 fix pami woard
2025-09-18 carte pami Raspberry
2026-03-21 Correction de iasserv et pamiboard
2026-03-21 schema pdf
2026-03-21 fix alimentation 12V et USB
